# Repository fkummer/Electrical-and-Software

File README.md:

# Electrical-and-Software
Repository for the 2016-2017 Electrical and Software subteam of CRT

We're using the GitFlow Workflow! SO DON'T COMMIT TO MASTER!!!!! Make pull requests into develop.

Learn more about GitFlow here: https://www.atlassian.com/git/tutorials/comparing-workflows/gitflow-workflow

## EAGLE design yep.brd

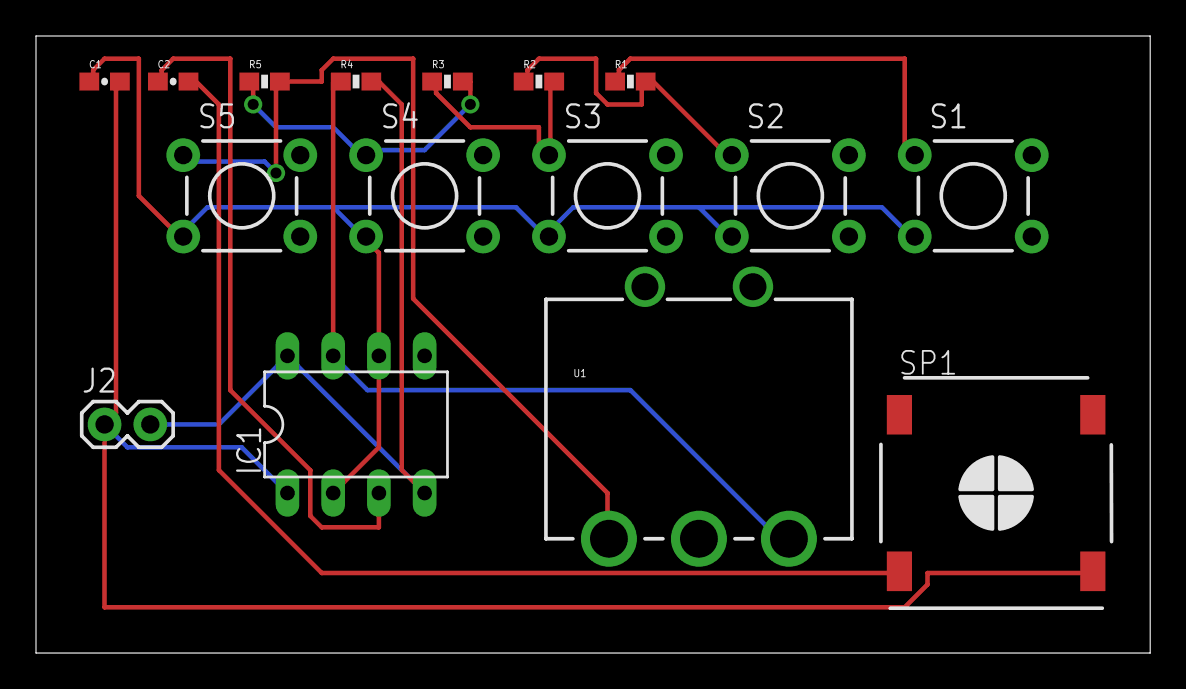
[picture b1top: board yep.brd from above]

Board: 2 copper layers, 61.9 x 34.3 mm, 16 parts (0 on the bottom side), 11 nets.

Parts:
C1: 100n; 0603-CAP
C2: 10u; 0603-CAP
IC1: NE555; DIL-08
J2: 1X02
R1, R2, R3, R5: 1k; 0603-RES
R4: 4.7k; 0603-RES
S1, S2, S3, S4, S5: TACTILE-PTH
SP1: 8Ohm; SMS-1308MS-2-R
U1: 10k; POT_PTH

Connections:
unnamed: IC1.4, IC1.8, J2.2, R4.2
unnamed: IC1.7, R4.1, U1.E@2
unnamed: R1.2, R2.1, S2.1
unnamed: R2.2, R3.1, S3.1
unnamed: R3.2, R5.1, S4.1
unnamed: R5.2, S5.1, U1.E@1
unnamed: R1.1, S1.1
unnamed: C1.1, IC1.2, IC1.6, S1.3, S2.3, S3.3, S4.3, S5.3
unnamed: C2.1, IC1.3
unnamed: C2.2, SP1.+
unnamed: C1.2, IC1.1, J2.1, SP1.-

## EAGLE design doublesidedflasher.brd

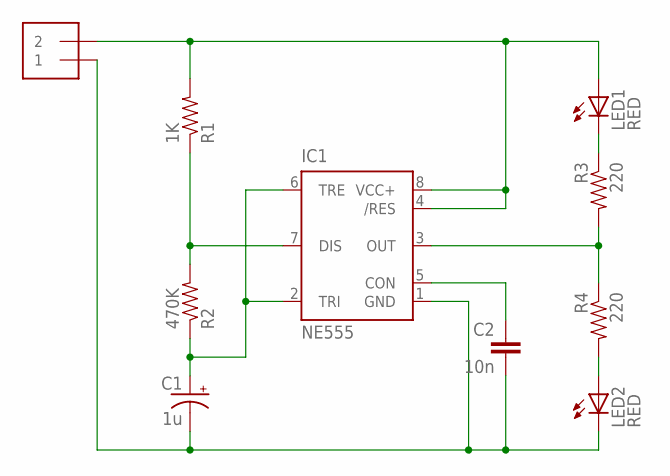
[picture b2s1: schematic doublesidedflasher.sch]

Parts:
C1: 1u; CPOL-RADIAL-10UF-25V
C2: 10n; CAP-PTH-SMALL
IC1: NE555; DIL-08
J1: 1X2-3.5MM
LED1, LED2: RED; LED5MM
R1: 1K; AXIAL-0.3
R2: 470K; AXIAL-0.3
R3, R4: 220; AXIAL-0.3

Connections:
GND: C1.2 (-), C2.2, IC1.1 (GND), J1.1, LED2.K (C)
unnamed: IC1.7 (DIS), R1.P$1 (1), R2.P$2 (2)
unnamed: LED2.A, R4.P$2 (2)
unnamed: LED1.K (C), R3.P$1 (1)
unnamed: IC1.3 (OUT), R3.P$2 (2), R4.P$1 (1)
unnamed: C1.1 (+), IC1.2 (TRI), IC1.6 (TRE), R2.P$1 (1)
unnamed: C2.1, IC1.5 (CON)
VCC+: IC1.4 (/RES), IC1.8 (VCC+), J1.2, LED1.A, R1.P$2 (2)

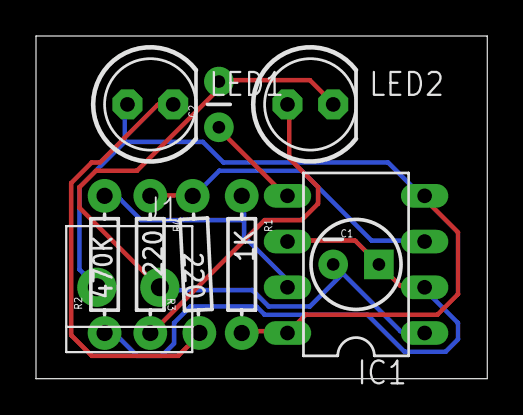
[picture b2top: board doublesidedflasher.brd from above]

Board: 2 copper layers, 25.1 x 19.0 mm, 10 parts (0 on the bottom side), 8 nets.

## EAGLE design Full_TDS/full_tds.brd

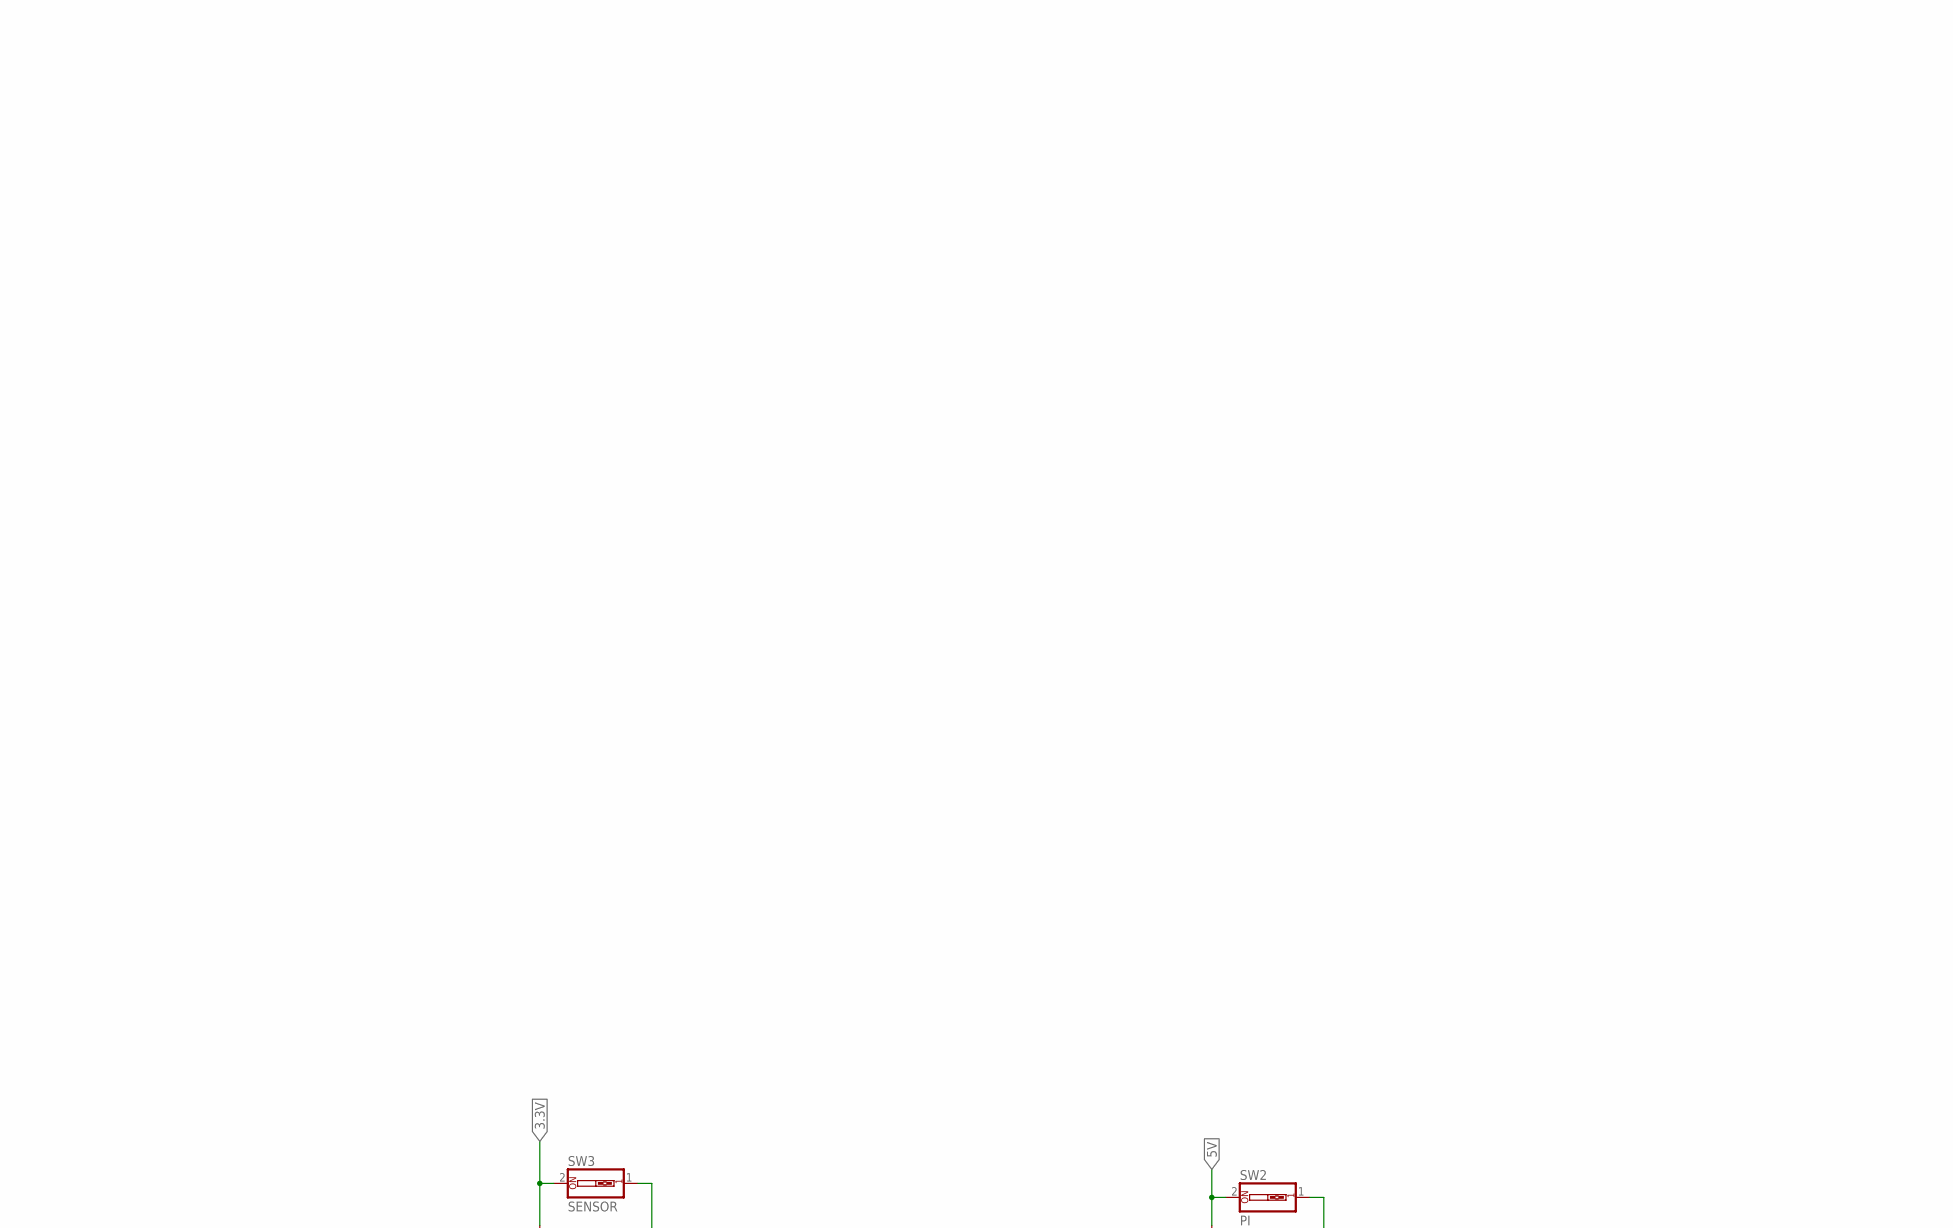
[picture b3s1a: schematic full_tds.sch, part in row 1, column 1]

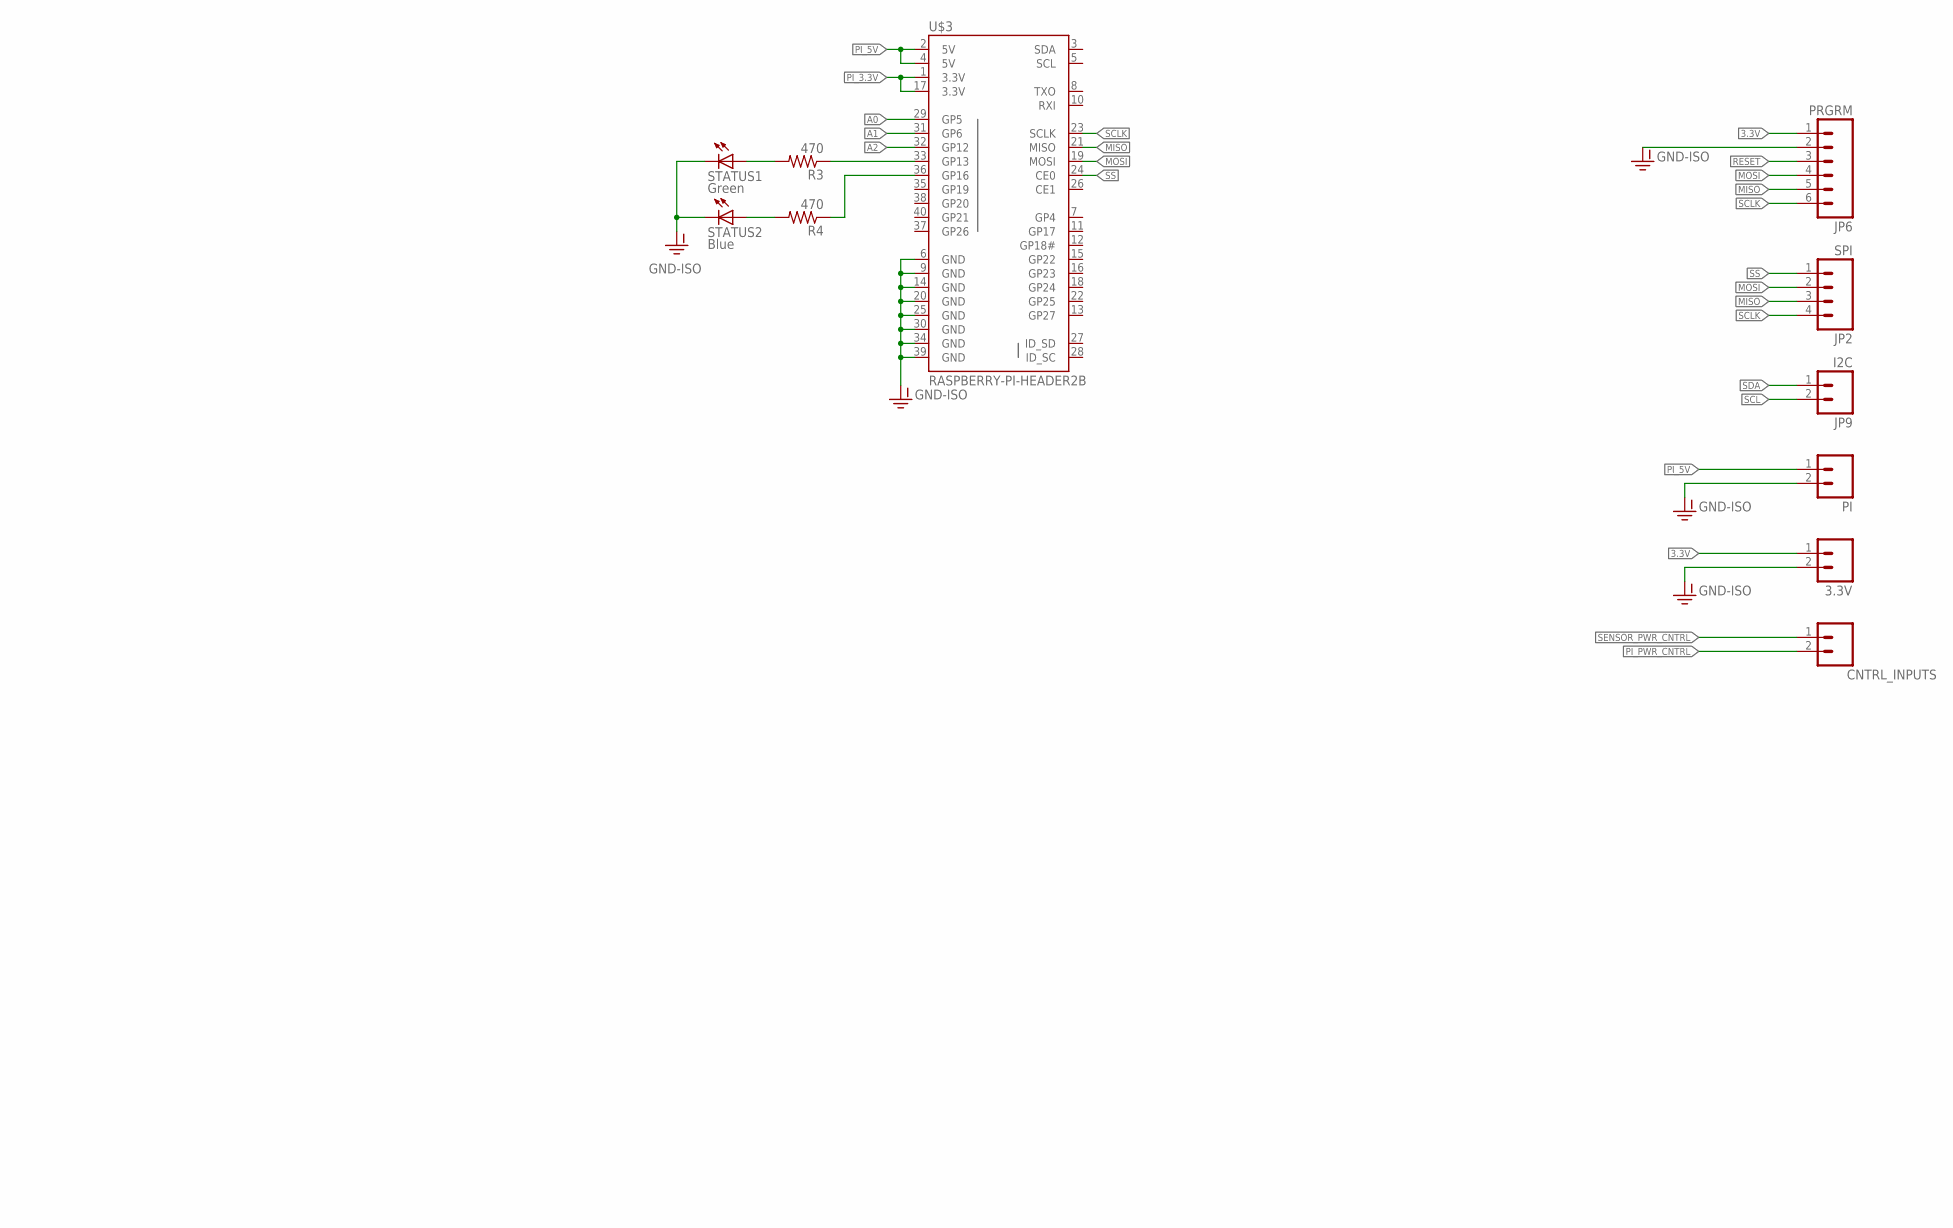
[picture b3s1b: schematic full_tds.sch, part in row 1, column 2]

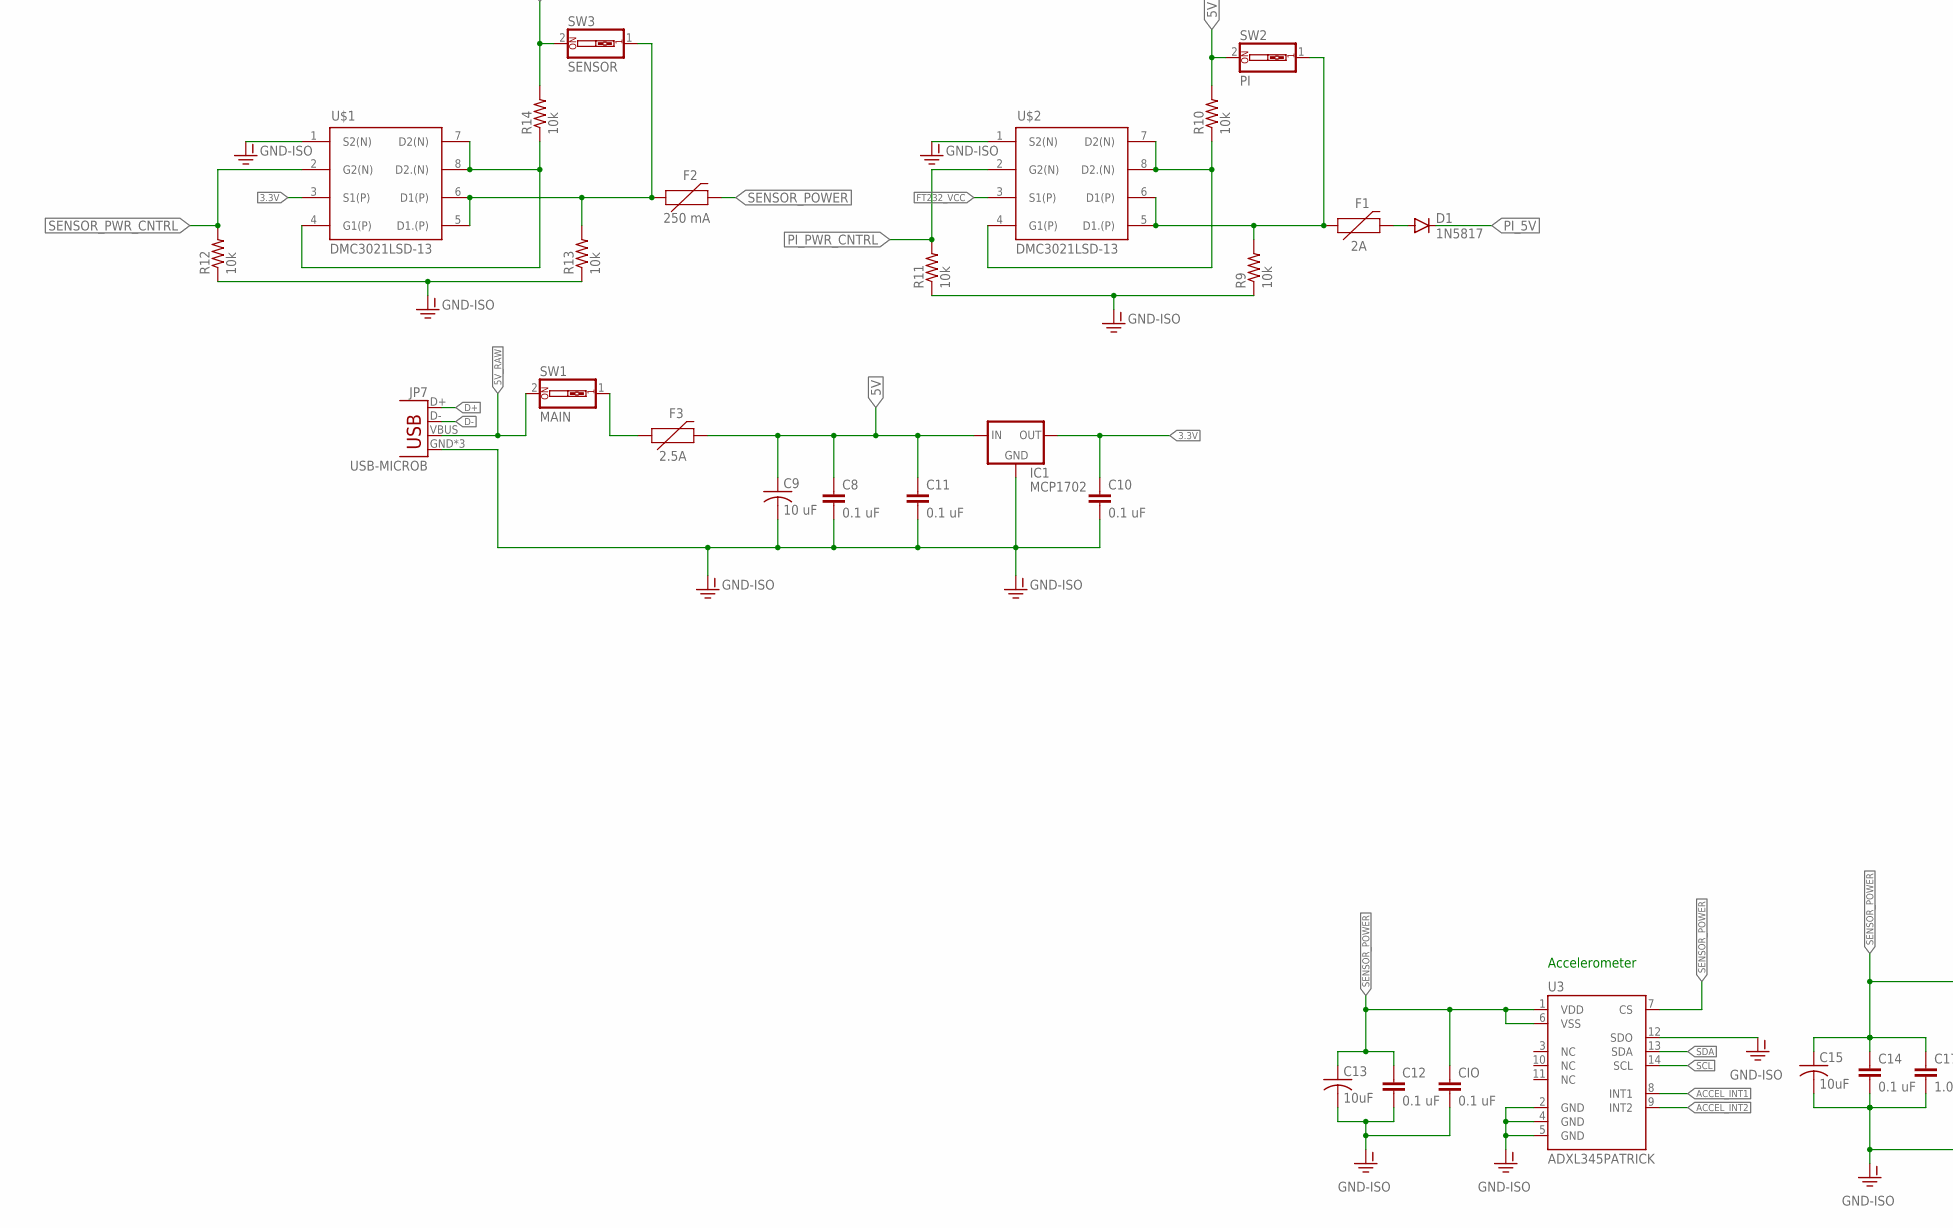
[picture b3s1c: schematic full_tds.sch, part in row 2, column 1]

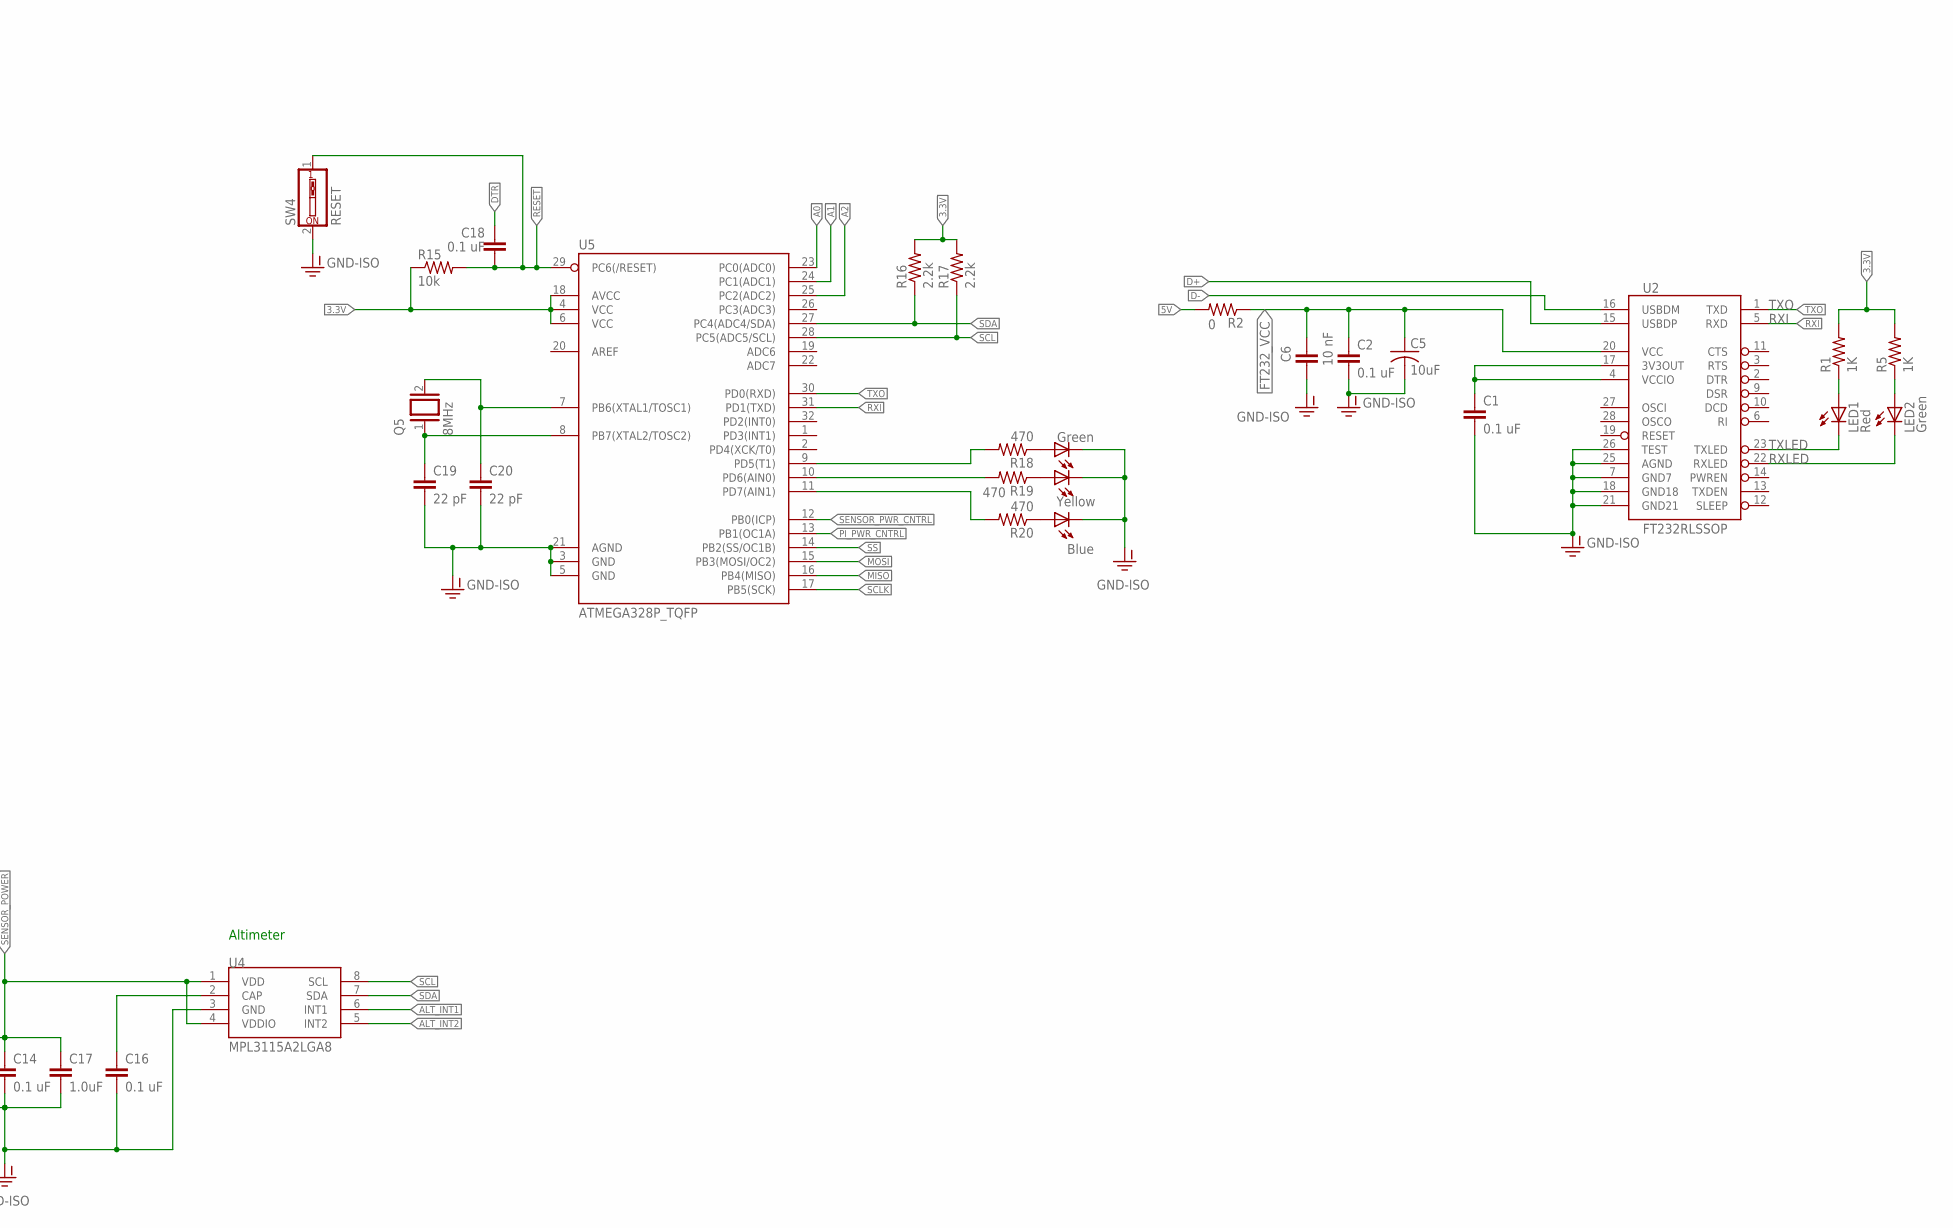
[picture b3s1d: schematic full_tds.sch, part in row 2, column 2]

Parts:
3.3V: M02PTH; 1X02
C1, C2, C8, C10, C11, C12, C14, C16, C18: 0.1 uF; 1206
C5, C13, C15: 10uF; C1206
C6: 10 nF; 1206
C9: 10 uF; C1206
C17: 1.0uF; 1206
C19, C20: 22 pF; 1206
CIO: 0.1 uF; 1206
CNTRL_INPUTS: M02PTH; 1X02
D1: 1N5817; DIODE-1N4001
F1: 2A; 1206
F2: 250 mA; 1206
F3: 2.5A; 1206
IC1: MCP1702; TO92
JP2: SPI; 1X04
JP6: PRGRM; 1X06
JP7: USB-MICROB
JP9: I2C; 1X02
LED1: Red; CHIPLED_1206
LED2, LED6: Green; CHIPLED_1206
LED7: Yellow; CHIPLED_1206
LED8: Blue; CHIPLED_1206
PI: M02PTH; 1X02
Q5: 8MHz; QS
R1, R5: 1K; 1206
R2: 0; 1206
R3, R4, R18, R19, R20: 470; 1206
R9, R10, R11, R12, R13, R14: 10k; R1206
R15: 10k; 1206
R16, R17: 2.2k; 1206
STATUS1: Green; CHIPLED_1206
STATUS2: Blue; CHIPLED_1206
SW1: MAIN; EDG-01
SW2: PI; EDG-01
SW3: SENSOR; EDG-01
SW4: RESET; EDG-01
U2: FT232RLSSOP; SSOP28DB
U3: ADXL345PATRICK; LGA14_1:1_PATRICK
U4: MPL3115A2LGA8; LGA8
U5: ATMEGA328P_TQFP; TQFP32-08
U$1, U$2: DMC3021LSD-13; SOIC-8
U$3: RASPBERRY-PI-HEADER2B; 2X20-NOSILK

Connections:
3.3V: 3.3V.1, C10.1, IC1.3 (OUT), JP6.1, R1.2, R5.2, R14.2, R15.1, R16.2, R17.2, SW3.2, U5.4 (VCC), U5.6 (VCC), U5.18 (AVCC), U$1.3 (S1(P))
5V: C8.1, C9.1, C11.1, F3.2, IC1.2 (IN), R2.2, R10.2, SW2.2
5V_RAW: JP7.VBUS, SW1.2
5V_SWITCH: F3.1, SW1.1
A0: U5.23 (PC0(ADC0)), U$3.29 (GP5)
A1: U5.24 (PC1(ADC1)), U$3.31 (GP6)
A2: U5.25 (PC2(ADC2)), U$3.32 (GP12)
ACCEL_INT1: U3.8 (INT1)
ACCEL_INT2: U3.9 (INT2)
ALT_INT1: U4.6 (INT1)
ALT_INT2: U4.5 (INT2)
D+: JP7.D+, U2.15 (USBDP)
D-: JP7.D-, U2.16 (USBDM)
DTR: C18.1
FT232_VCC: C2.1, C5.1, C6.2, R2.1, U2.20 (VCC), U$2.3 (S1(P))
FUSE_DIODE_PI: D1.A, F1.2
GND-ISO: 3.3V.2, C1.2, C2.2, C5.2, C6.1, C8.2, C9.2, C10.2, C11.2, C12.2, C13.2, C14.2, C15.2, C16.2, C17.2, C19.2, C20.2, CIO.2, IC1.1 (GND), JP6.2, JP7.GND, JP7.MT1 (GND), JP7.MT2 (GND), LED6.C, LED7.C, LED8.C, PI.2, R9.1, R11.1, R12.1, R13.1, STATUS1.C, STATUS2.C, SW4.2, U2.7 (GND7), U2.18 (GND18), U2.21 (GND21), U2.25 (AGND), U2.26 (TEST), U3.2 (GND), U3.4 (GND), U3.5 (GND), U3.12 (SDO), U4.3 (GND), U5.3 (GND), U5.5 (GND), U5.21 (AGND), U$1.1 (S2(N)), U$2.1 (S2(N)), U$3.6 (GND), U$3.9 (GND), U$3.14 (GND), U$3.20 (GND), U$3.25 (GND), U$3.30 (GND), U$3.34 (GND), U$3.39 (GND)
GP13: R3.1, U$3.33 (GP13)
GP16: R4.1, U$3.36 (GP16)
MISO: JP2.3, JP6.5, U5.16 (PB4(MISO)), U$3.21 (MISO)
MOSI: JP2.2, JP6.4, U5.15 (PB3(MOSI/OC2)), U$3.19 (MOSI)
unnamed: LED1.A, R1.1
unnamed: LED2.A, R5.1
unnamed: R4.2, STATUS2.A
unnamed: R3.2, STATUS1.A
unnamed: C16.1, U4.2 (CAP)
unnamed: LED6.A, R18.1
unnamed: LED7.A, R19.1
unnamed: LED8.A, R20.1
PD5: R18.2, U5.9 (PD5(T1))
PD6: R19.2, U5.10 (PD6(AIN0))
PD7: R20.2, U5.11 (PD7(AIN1))
PI_3.3V: U$3.1 (3.3V), U$3.17 (3.3V)
PI_5V: D1.C, PI.1, U$3.2 (5V), U$3.4 (5V)
PI_N_DRAIN: R10.1, U$2.4 (G1(P)), U$2.7 (D2(N)), U$2.8 (D2.(N))
PI_PWR_CNTRL: CNTRL_INPUTS.2, R11.2, U5.13 (PB1(OC1A)), U$2.2 (G2(N))
PI_P_DRAIN: F1.1, R9.2, SW2.1, U$2.5 (D1.(P)), U$2.6 (D1(P))
RESET: C18.2, JP6.3, R15.2, SW4.1, U5.29 (PC6(/RESET))
RXI: U2.5 (RXD), U5.31 (PD1(TXD))
RXLED: LED2.C, U2.22 (RXLED)
SCL: JP9.2, R17.1, U3.14 (SCL), U4.8 (SCL), U5.28 (PC5(ADC5/SCL))
SCLK: JP2.4, JP6.6, U5.17 (PB5(SCK)), U$3.23 (SCLK)
SDA: JP9.1, R16.1, U3.13 (SDA), U4.7 (SDA), U5.27 (PC4(ADC4/SDA))
SENSOR_POWER: C12.1, C13.1, C14.1, C15.1, C17.1, CIO.1, F2.2, U3.1 (VDD), U3.6 (VSS), U3.7 (CS), U4.1 (VDD), U4.4 (VDDIO)
SENSOR_PWR_CNTRL: CNTRL_INPUTS.1, R12.2, U5.12 (PB0(ICP)), U$1.2 (G2(N))
SENS_N_DRAIN: R14.1, U$1.4 (G1(P)), U$1.7 (D2(N)), U$1.8 (D2.(N))
SENS_P_DRAIN: F2.1, R13.2, SW3.1, U$1.5 (D1.(P)), U$1.6 (D1(P))
SS: JP2.1, U5.14 (PB2(SS/OC1B)), U$3.24 (CE0)
TXLED: LED1.C, U2.23 (TXLED)
TXO: U2.1 (TXD), U5.30 (PD0(RXD))
VCCIO: C1.1, U2.4 (VCCIO), U2.17 (3V3OUT)
XTAL1: C20.1, Q5.2, U5.7 (PB6(XTAL1/TOSC1))
XTAL2: C19.1, Q5.1, U5.8 (PB7(XTAL2/TOSC2))

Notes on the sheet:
Altimeter
Accelerometer

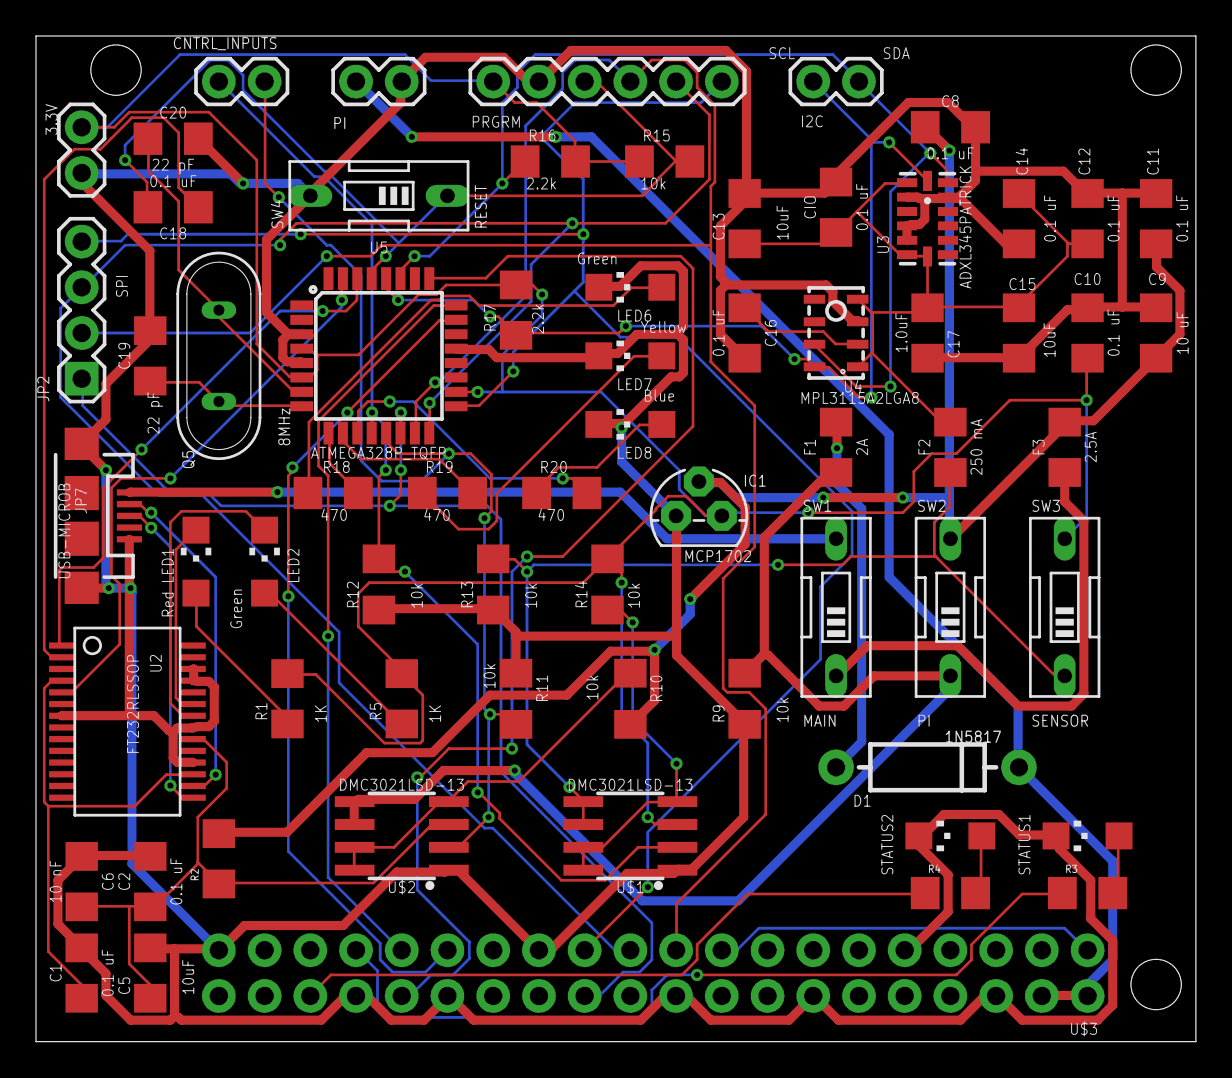
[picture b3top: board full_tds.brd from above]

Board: 2 copper layers, 64.4 x 55.9 mm, 66 parts (0 on the bottom side), 48 nets.

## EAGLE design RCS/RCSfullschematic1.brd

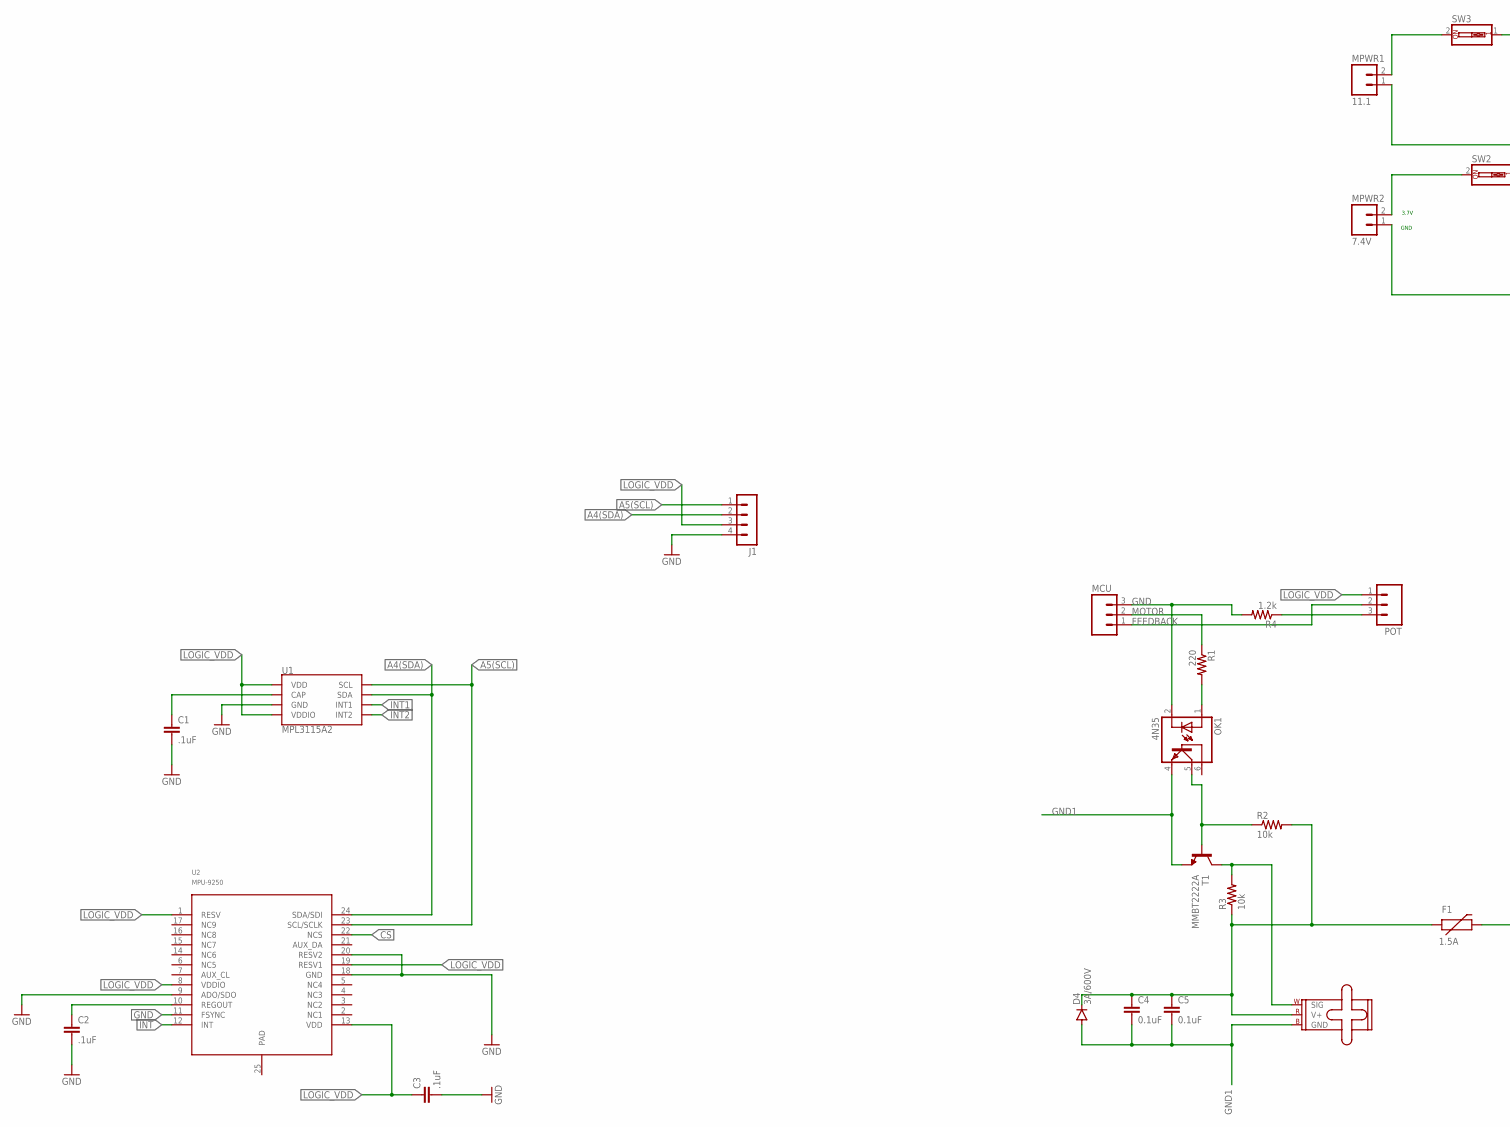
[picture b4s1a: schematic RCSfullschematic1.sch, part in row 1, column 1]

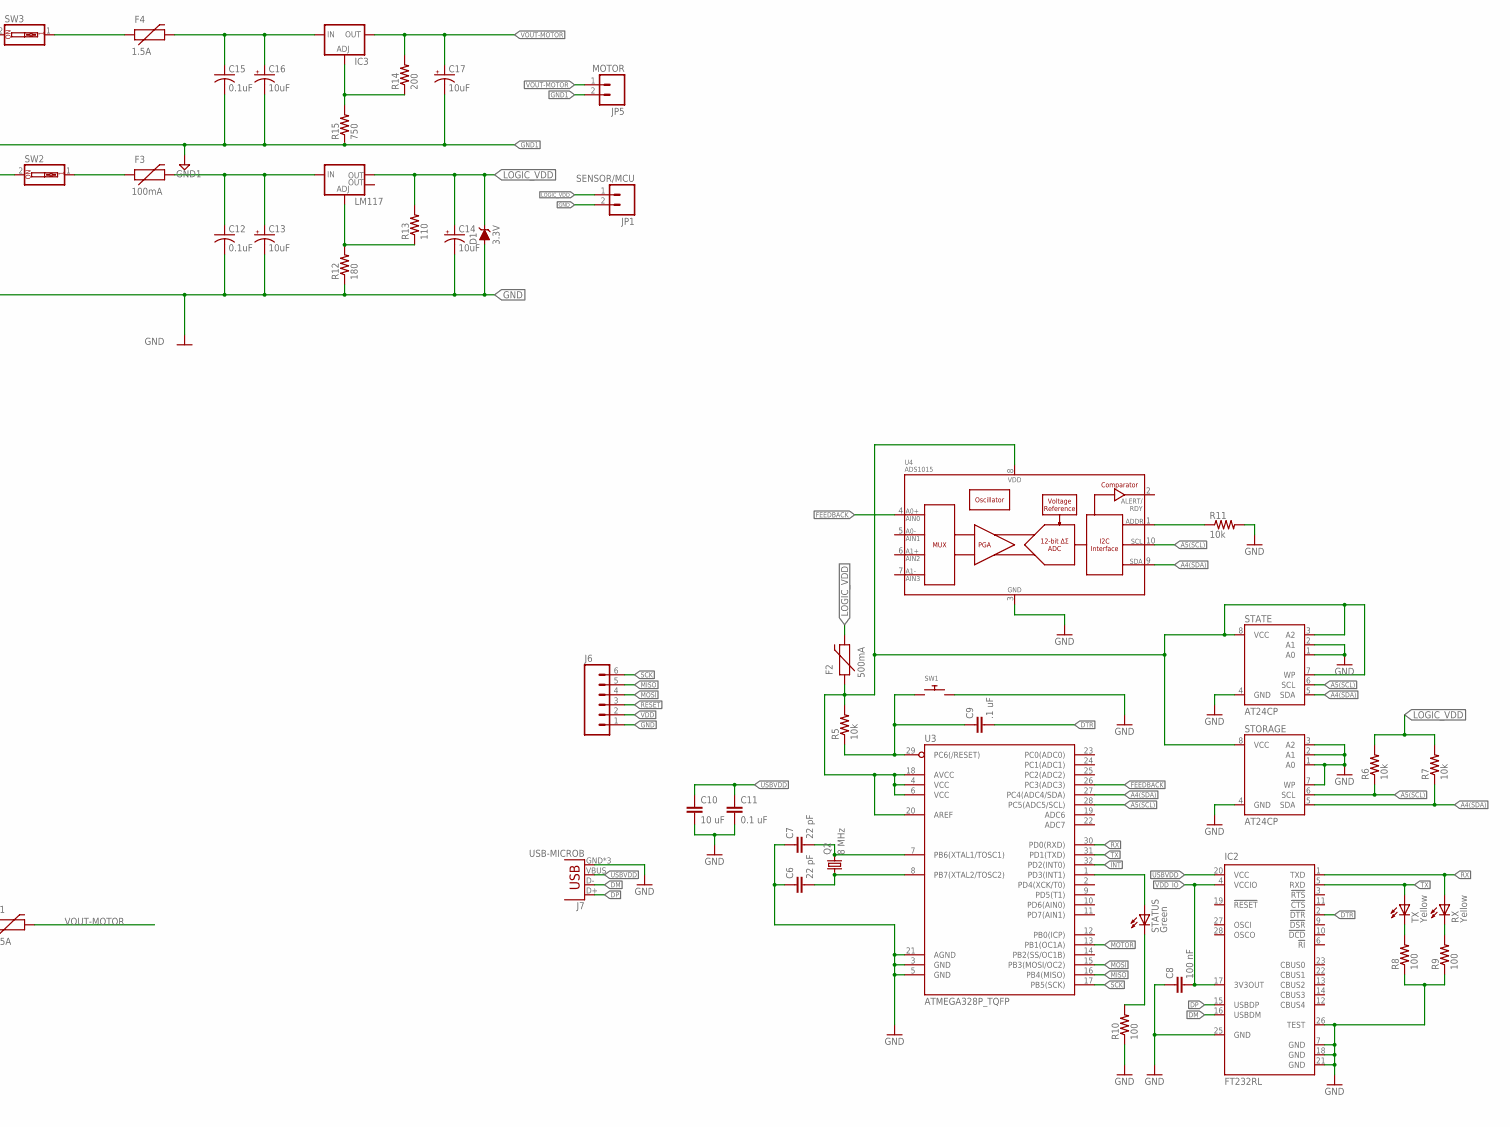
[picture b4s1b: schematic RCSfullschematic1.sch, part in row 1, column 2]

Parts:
C1, C2, C3: .1uF; 1206
C4, C5: 0.1uF; 1206
C6, C7: 22 pF; C1206
C8: 100 nF; C1206
C9: .1 uF; C1206
C10: 10 uF; C1206
C11: 0.1 uF; C1206
C12, C15: 0.1uF; C1206
C13, C14, C16, C17: 10uF; EIA3216
D1: 3.3V; SOD-323@2
D4: 3A/600V; SMA-DIODE_ALT
F1, F4: 1.5A; PTC-1206
F2: 500mA; PTC-1206
F3: 100mA; PTC-1206
IC2: FT232RL; SSOP28
IC3: LM317TS; 317TS
J1: MA04-1
J6: M06LOCK; 1X06_LOCK
J7: USB-MICROB
JP1: SENSOR/MCU; 1X02
JP5: MOTOR; 1X02
LM117: V_REG_LM1117SOT223; SOT223
MCU: M03PTH; 1X03
MPWR1: 11.1; 1X02
MPWR2: 7.4V; 1X02
OK1: 4N35; DIL06
POT: M03PTH; 1X03
Q2: 8 MHz; HC49/S
R1: 220; 1206
R2, R3: 10k; 1206
R4: 1.2k; 1206
R5, R6, R7, R11: 10k; R1206
R8, R9, R10: 100; R1206
R12: 180; M1206
R13: 110; M1206
R14: 200; M1206
R15: 750; M1206
RX: Yellow; CHIPLED_1206
SERVO: SMALL_SERVO; 1X03
STATE: AT24CP; DIL08
STATUS: Green; CHIPLED_1206
STORAGE: AT24CP; DIL08
SW1: SWITCH_PUSHBUTTONSOFTTOUCHSMD_SJ; PUSHBUTTON_SMD_SJ
SW2, SW3: SW_DIP-1; EDG-01
T1: MMBT2222A; SOT23-3
TX: Yellow; CHIPLED_1206
U1: MPL3115A2; LGA-8
U2: MPU-9250; LEAD-QFN24
U3: ATMEGA328P_TQFP; TQFP32-08
U4: ADS1015; MSOP10

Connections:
6V_POWER: C4.1, C5.1, D4.C, F1.1, R2.2, R3.1, SERVO.2 (V+)
A4(SDA): J1.2, R7.1, STATE.5 (SDA), STORAGE.5 (SDA), U1.7 (SDA), U2.24 (SDA/SDI), U3.27 (PC4(ADC4/SDA)), U4.9 (SDA)
A5(SCL): J1.1, R6.1, STATE.6 (SCL), STORAGE.6 (SCL), U1.8 (SCL), U2.23 (SCL/SCLK), U3.28 (PC5(ADC5/SCL)), U4.10 (SCL)
CS: U2.22 (NCS)
DM: IC2.16 (USBDM), J7.D-
DP: IC2.15 (USBDP), J7.D+
DTR: C9.2, IC2.2 (!DTR)
FEEDBACK: MCU.1, POT.2, U3.26 (PC3(ADC3)), U4.4 (AIN0)
GND: C1.2, C2.2, C3.2, C6.1, C7.1, C8.1, C10.2, C11.2, C12.2, C13.-, C14.-, D1.A, IC2.7 (GND), IC2.18 (GND), IC2.21 (GND), IC2.25 (GND), IC2.26 (TEST), J1.4, J6.1, J7.GND, J7.MT1 (GND), J7.MT2 (GND), JP1.2, MCU.3, MPWR2.1, OK1.2 (C), R4.2, R8.1, R9.1, R10.1, R11.2, R12.1, STATE.1 (A0), STATE.2 (A1), STATE.4 (GND), STORAGE.1 (A0), STORAGE.2 (A1), STORAGE.3 (A2), STORAGE.4 (GND), STORAGE.7 (WP), SW1.P$2, U1.3 (GND), U2.9 (ADO/SDO), U2.11 (FSYNC), U2.18 (GND), U2.20 (RESV2), U3.3 (GND), U3.5 (GND), U3.21 (AGND), U4.3 (VSS); also elsewhere on the board
GND1: C4.2, C5.2, C15.2, C16.-, C17.-, D4.A, JP5.2, MPWR1.1, OK1.4 (EMI), R15.1, SERVO.3 (GND), T1.2 (E)
INT: U2.12 (INT), U3.32 (PD2(INT0))
INT1: U1.6 (INT1)
INT2: U1.5 (INT2)
LOGIC_VDD: C3.1, C14.+, D1.C, F2.2, J1.3, JP1.1, LM117.2 (OUT), POT.1, R6.2, R7.2, R13.2, U1.1 (VDD), U1.4 (VDDIO), U2.1 (RESV), U2.8 (VDDIO), U2.13 (VDD), U2.19 (RESV1)
MISO: J6.5, U3.16 (PB4(MISO))
MOSI: J6.4, U3.15 (PB3(MOSI/OC2))
MOTOR: MCU.2, R1.1, U3.13 (PB1(OC1A))
unnamed: C1.1, U1.2 (CAP)
unnamed: OK1.5 (COL), R2.1, T1.1 (B)
unnamed: C2.1, U2.10 (REGOUT)
unnamed: POT.3, R4.1
unnamed: R11.1, U4.1 (ADDR)
unnamed: OK1.1 (A), R1.2
unnamed: C7.2, Q2.2, U3.7 (PB6(XTAL1/TOSC1))
unnamed: C6.2, Q2.1, U3.8 (PB7(XTAL2/TOSC2))
unnamed: R8.2, TX.C
unnamed: R9.2, RX.C
unnamed: STATUS.A, U3.1 (PD3(INT1))
unnamed: R10.2, STATUS.C
unnamed: LM117.1 (ADJ), R12.2, R13.1
unnamed: MPWR2.2, SW2.2
unnamed: C12.1, C13.+, F3.2, LM117.3 (IN)
unnamed: F3.1, SW2.1
unnamed: MPWR1.2, SW3.2
unnamed: F4.1, SW3.1
unnamed: C15.1, C16.+, F4.2, IC3.3 (IN)
unnamed: IC3.1 (ADJ), R14.1, R15.2
unnamed 38: U3.2 (PD4(XCK/T0)); also elsewhere on the board
RESET: C9.1, J6.3, R5.1, SW1.P$1, U3.29 (PC6(/RESET))
RX: IC2.1 (TXD), RX.A, U3.30 (PD0(RXD))
SCK: J6.6, U3.17 (PB5(SCK))
SIGNAL: R3.2, SERVO.1 (SIG), T1.3 (C)
TX: IC2.5 (RXD), TX.A, U3.31 (PD1(TXD))
USBVDD: C10.1, C11.1, IC2.20 (VCC), J7.VBUS
VCC: F2.1, R5.2, STATE.3 (A2), STATE.7 (WP), STATE.8 (VCC), STORAGE.8 (VCC), U3.4 (VCC), U3.6 (VCC), U3.18 (AVCC), U3.20 (AREF), U4.8 (VDD)
VDD: J6.2
VDD_IO: C8.2, IC2.4 (VCCIO), IC2.17 (3V3OUT)
VOUT-MOTOR: C17.+, F1.2, IC3.2 (OUT), JP5.1, R14.2

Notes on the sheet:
3.7V
GND

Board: 2 copper layers, 68 parts (0 on the bottom side), 45 nets, no tracks yet.

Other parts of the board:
ERROR: Red; CHIPLED_1206
R16: 100; R1206

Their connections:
GND: R16.1; also elsewhere on the board
unnamed: ERROR.C, R16.2
unnamed 38: ERROR.A; also elsewhere on the board

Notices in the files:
parts and their libraries:
SparkFun-Passives: Licensing: Creative Commons ShareAlike 4.0 International - https://creativecommons.org/licenses/by-sa/4.0
SparkFun-Sensors: Licensing: CC v3.0 Share-Alike You are welcome to use this library for commercial purposes.
